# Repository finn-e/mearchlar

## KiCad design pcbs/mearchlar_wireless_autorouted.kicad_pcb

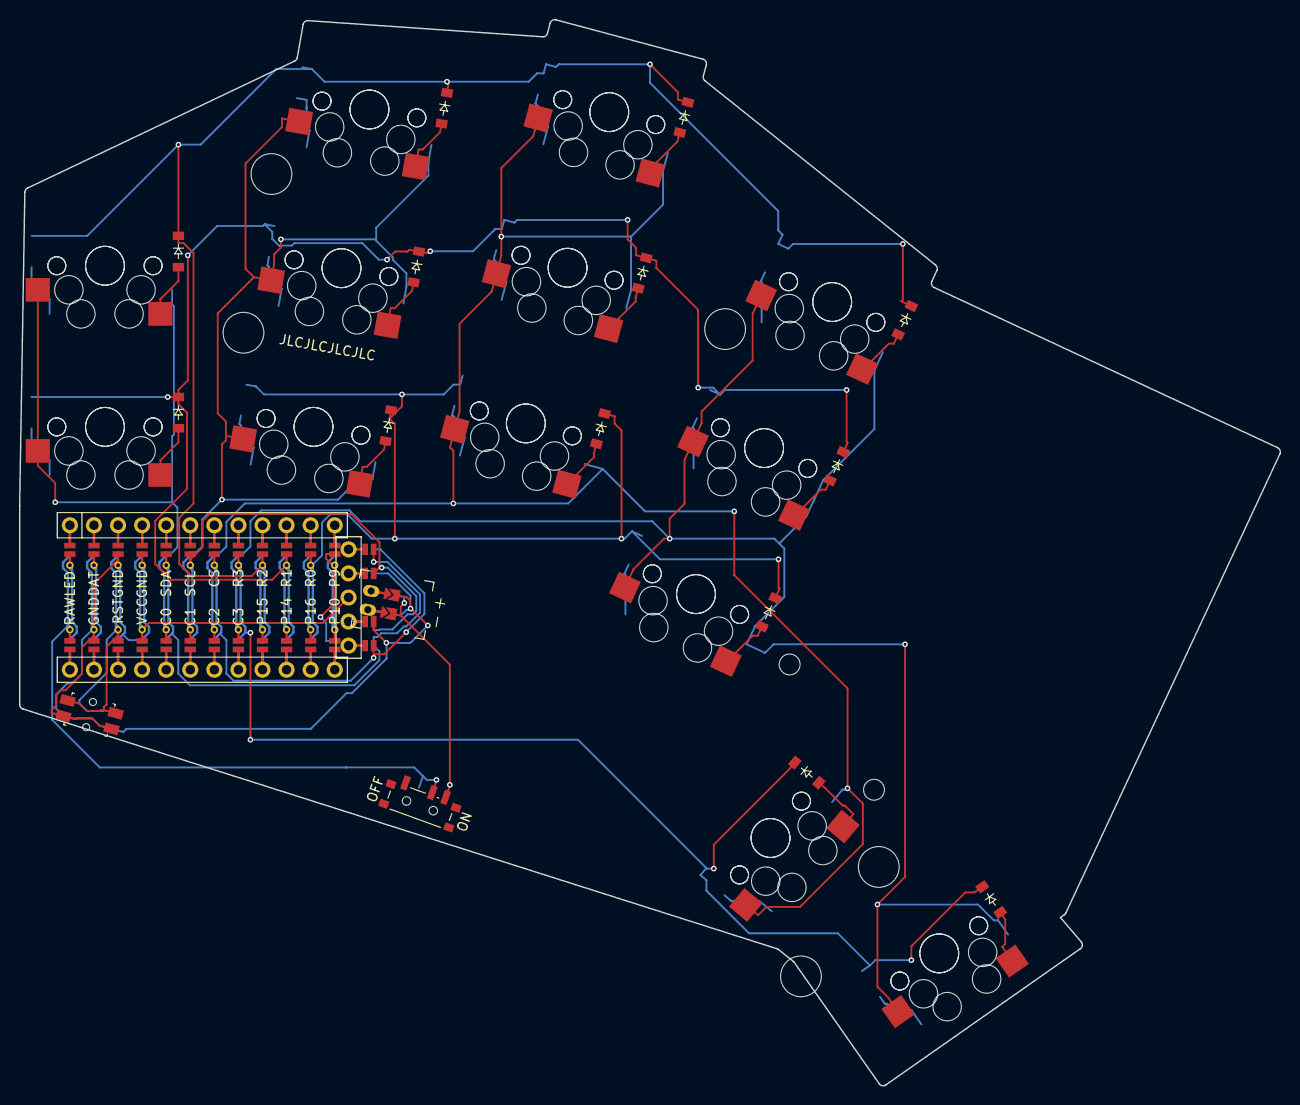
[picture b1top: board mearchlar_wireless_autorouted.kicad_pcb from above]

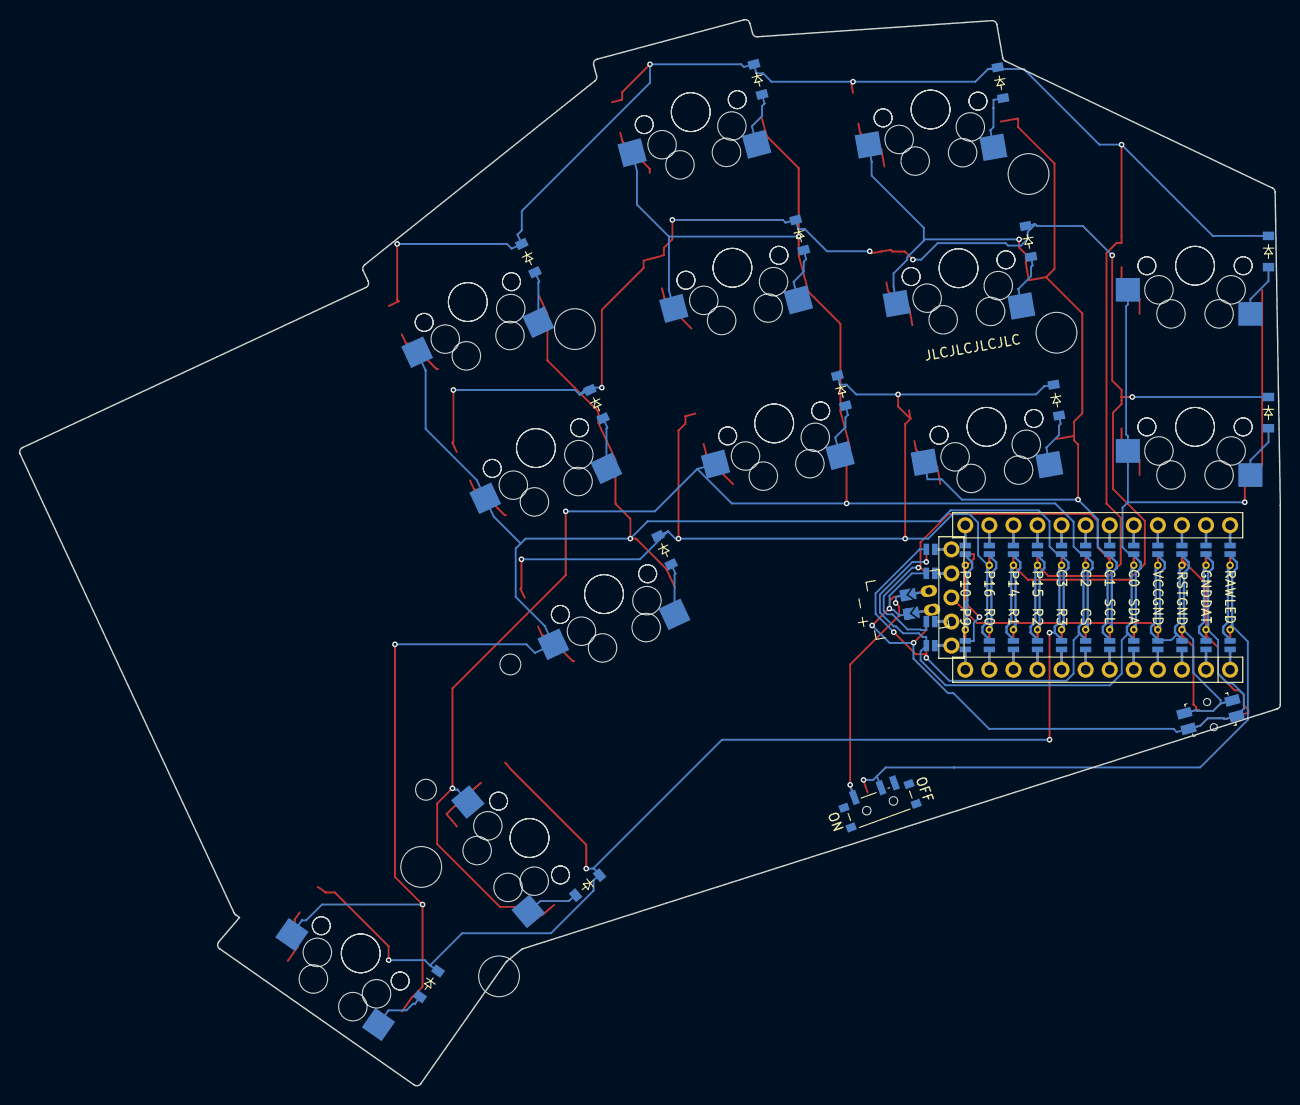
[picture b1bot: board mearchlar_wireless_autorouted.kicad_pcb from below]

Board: 2 copper layers, 133.0 x 112.5 mm, 64 parts (26 on the bottom side), 48 nets.

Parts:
D1, D2, D3, D4, D5, D6, D7, D8, D9, D10, D11, D12, D13, D14, D15, D16, D17, D18, D19, D20, D21, D22, D23, D24, D25, D26: diode_tht_sod123
DISP1: display_nice_view
JST1: battery_connector_jst_ph_2
MCU1: mcu_supermini_nrf52840
MH1, MH2, MH3, MH4, MH5, MH6, MH7: mounting_hole_npth
PWR1: power_switch_smd_side
RST1: reset_switch_smd_side
S1, S2, S3, S4, S5, S6, S7, S8, S9, S10, S11, S12, S13, S14, S15, S16, S17, S18, S19, S20, S21, S22, S23, S24, S25, S26: switch_mx

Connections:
BAT_P: JST1.1, PWR1.1, PWR1.3
C0: MCU1.120, S1.1, S2.1, S14.1, S15.1
C1: MCU1.119, S3.1, S4.1, S5.1, S16.1, S17.1, S18.1
C2: MCU1.118, S6.1, S7.1, S8.1, S12.1, S19.1, S20.1, S21.1, S25.1
C3: MCU1.117, S9.1, S10.1, S11.1, S13.1, S22.1, S23.1, S24.1, S26.1
CS: DISP1.10, DISP1.20, MCU1.107
DISP1_1: DISP1.1, DISP1.14, DISP1.27
DISP1_2: DISP1.2, DISP1.15, DISP1.26
DISP1_4: DISP1.4, DISP1.16, DISP1.25
DISP1_5: DISP1.5, DISP1.17, DISP1.24
GND: DISP1.11, DISP1.21, JST1.2, MCU1.103, MCU1.104, MCU1.123, RST1.1, RST1.3
JST1_1: JST1.11, JST1.21, JST1.31
JST1_2: JST1.12, JST1.22, JST1.32
R0: D3.1, D6.1, D9.1, D16.1, D19.1, D22.1, MCU1.111
R1: D1.1, D4.1, D7.1, D10.1, D14.1, D17.1, D20.1, D23.1, MCU1.110
R2: D2.1, D5.1, D8.1, D11.1, D15.1, D18.1, D21.1, D24.1, MCU1.109
R3: D12.1, D13.1, D25.1, D26.1, MCU1.108
RAW: MCU1.124, PWR1.2
RST: MCU1.122, RST1.2, RST1.4
SCL: DISP1.12, DISP1.22, MCU1.106
SDA: DISP1.13, DISP1.23, MCU1.105
VCC: DISP1.3, MCU1.121
far_home_B: D13.2, S13.2
far_home_F: D26.2, S26.2
index_bottom_B: D9.2, S9.2
index_bottom_F: D22.2, S22.2
index_home_B: D10.2, S10.2
index_home_F: D23.2, S23.2
index_top_B: D11.2, S11.2
index_top_F: D24.2, S24.2
middle_bottom_B: D6.2, S6.2
middle_bottom_F: D19.2, S19.2
middle_home_B: D7.2, S7.2
middle_home_F: D20.2, S20.2
middle_top_B: D8.2, S8.2
middle_top_F: D21.2, S21.2
near_home_B: D12.2, S12.2
near_home_F: D25.2, S25.2
pinky_home_B: D1.2, S1.2
pinky_home_F: D14.2, S14.2
pinky_top_B: D2.2, S2.2
pinky_top_F: D15.2, S15.2
ring_bottom_B: D3.2, S3.2
ring_bottom_F: D16.2, S16.2
ring_home_B: D4.2, S4.2
ring_home_F: D17.2, S17.2
ring_top_B: D5.2, S5.2
ring_top_F: D18.2, S18.2

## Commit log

2025-05-19 First commit? Second?
2025-05-19 Added 5-way and Azoteq Trackpad footprints Put them on board. Should be easier than modifying it in KiCad every time.
